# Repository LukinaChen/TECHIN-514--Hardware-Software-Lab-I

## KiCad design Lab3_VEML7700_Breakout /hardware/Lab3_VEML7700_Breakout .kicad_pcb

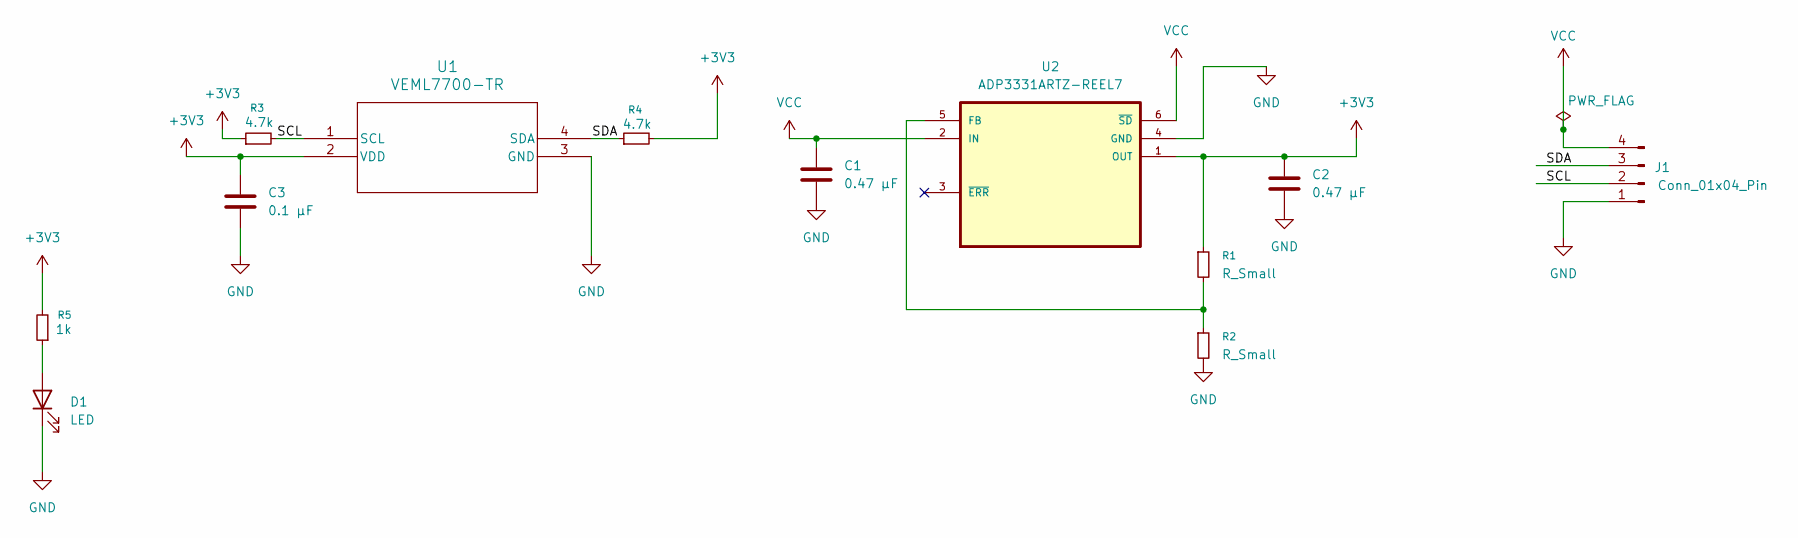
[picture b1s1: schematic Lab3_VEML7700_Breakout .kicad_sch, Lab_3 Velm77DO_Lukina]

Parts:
C1, C2: 0.47 µF; C_0805_2012Metric
C3: 0.1 µF; C_0805_2012Metric
D1: LED; LED_0805_2012Metric
J1: Conn_01x04_Pin; PinHeader_1x04_P2.54mm_Vertical
R1, R2: R_Small; R_0805_2012Metric
R3, R4: 4.7k; R_0805_2012Metric
R5: 1k; R_0805_2012Metric
U1: VEML7700-TR
U2: ADP3331ARTZ-REEL7; SOT-23-6

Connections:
+3V3: C2.1, C3.1, R1.1, R3.1, R4.2, R5.2, U1.2 (VDD), U2.1 (OUT)
/SCL: J1.2, R3.2, U1.1 (SCL)
/SDA: J1.3, R4.1, U1.4 (SDA)
GND: C1.2, C2.2, C3.2, D1.1 (K), J1.1, R2.2, U1.3 (GND), U2.4 (GND)
unnamed: D1.2 (A), R5.1
unnamed: R1.2, R2.1, U2.5 (FB)
VCC: C1.1, J1.4, U2.2 (IN), U2.6 (~SD)

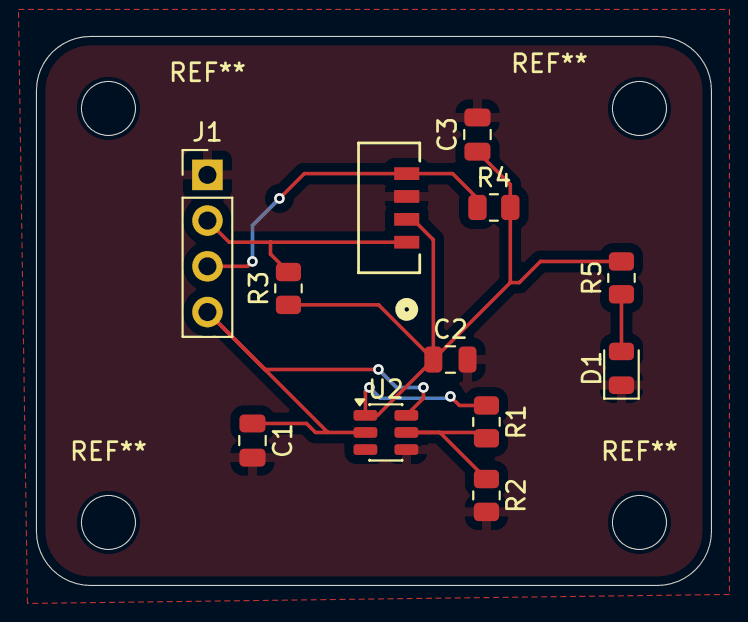
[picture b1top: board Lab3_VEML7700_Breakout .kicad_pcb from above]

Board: 2 copper layers, 37.5 x 30.5 mm, 12 parts (0 on the bottom side), 7 nets.

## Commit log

2026-01-08 Add files via upload
    Assignment1
2026-01-14 Organize files into Week1 and Lab2
2026-01-28 Lab4assignment
2026-01-30 Lab3-pcb design & lab4withnochanges
2026-02-05 Lab5-battery
2026-02-12 Lab6- Enclosure design
